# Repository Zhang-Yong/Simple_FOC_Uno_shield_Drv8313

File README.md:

# Simple_FOC_Uno_shield_Drv8313
My Open Source Arduion Uno R3 BLDC FOC shield, use Drv8313 chip
KICAD5 Source file 
Optimze Layout, connect DGND with DRV8313 GND,adding I2C connector for AS5600
Tested work with simplefoc Arduino software
A Try Version for my standalone customerized FOC controller

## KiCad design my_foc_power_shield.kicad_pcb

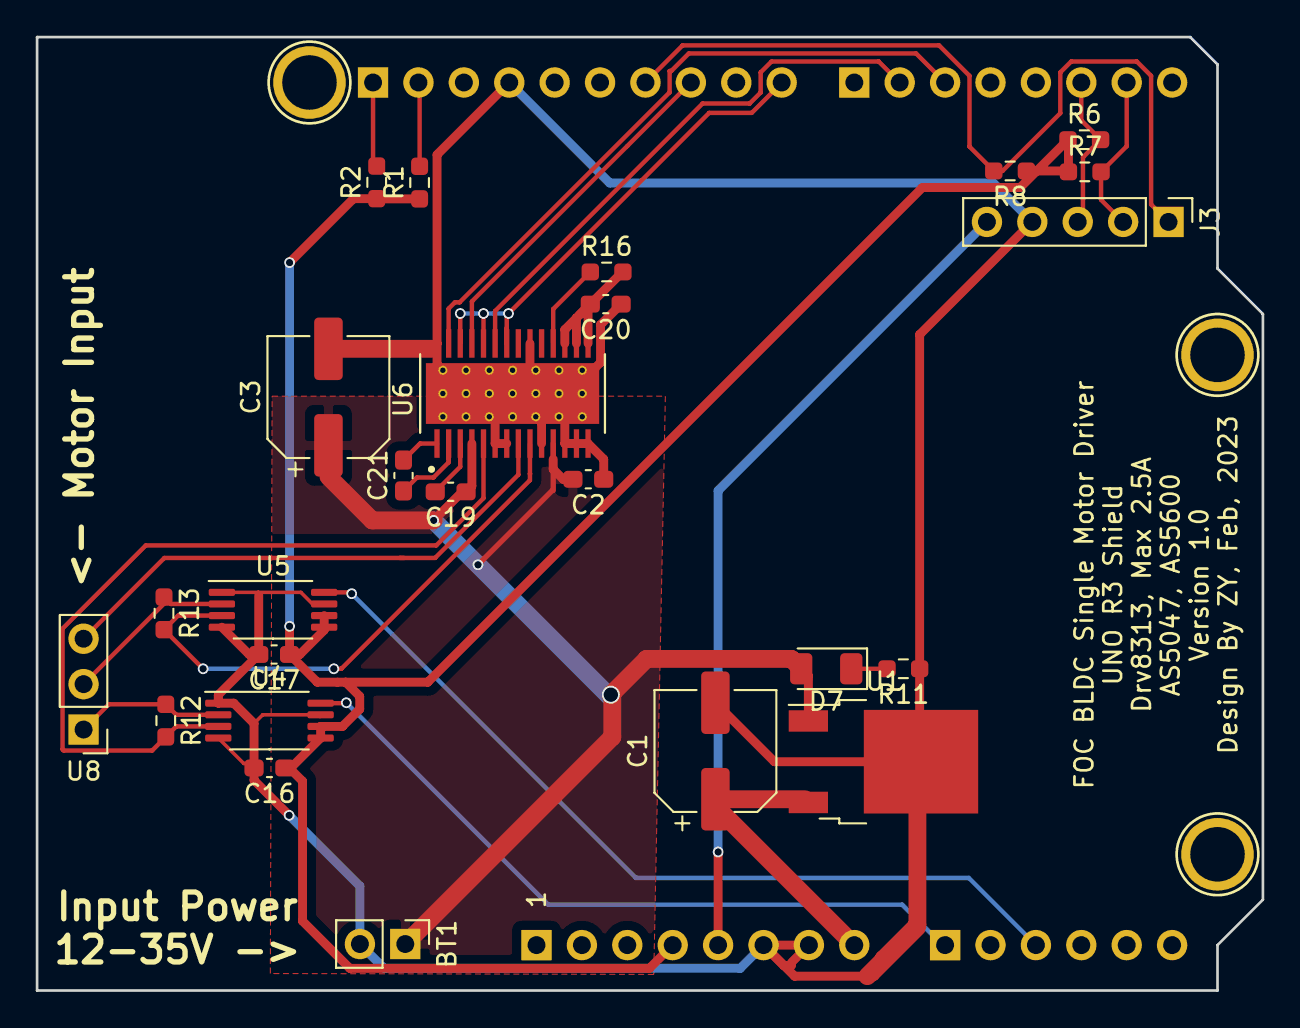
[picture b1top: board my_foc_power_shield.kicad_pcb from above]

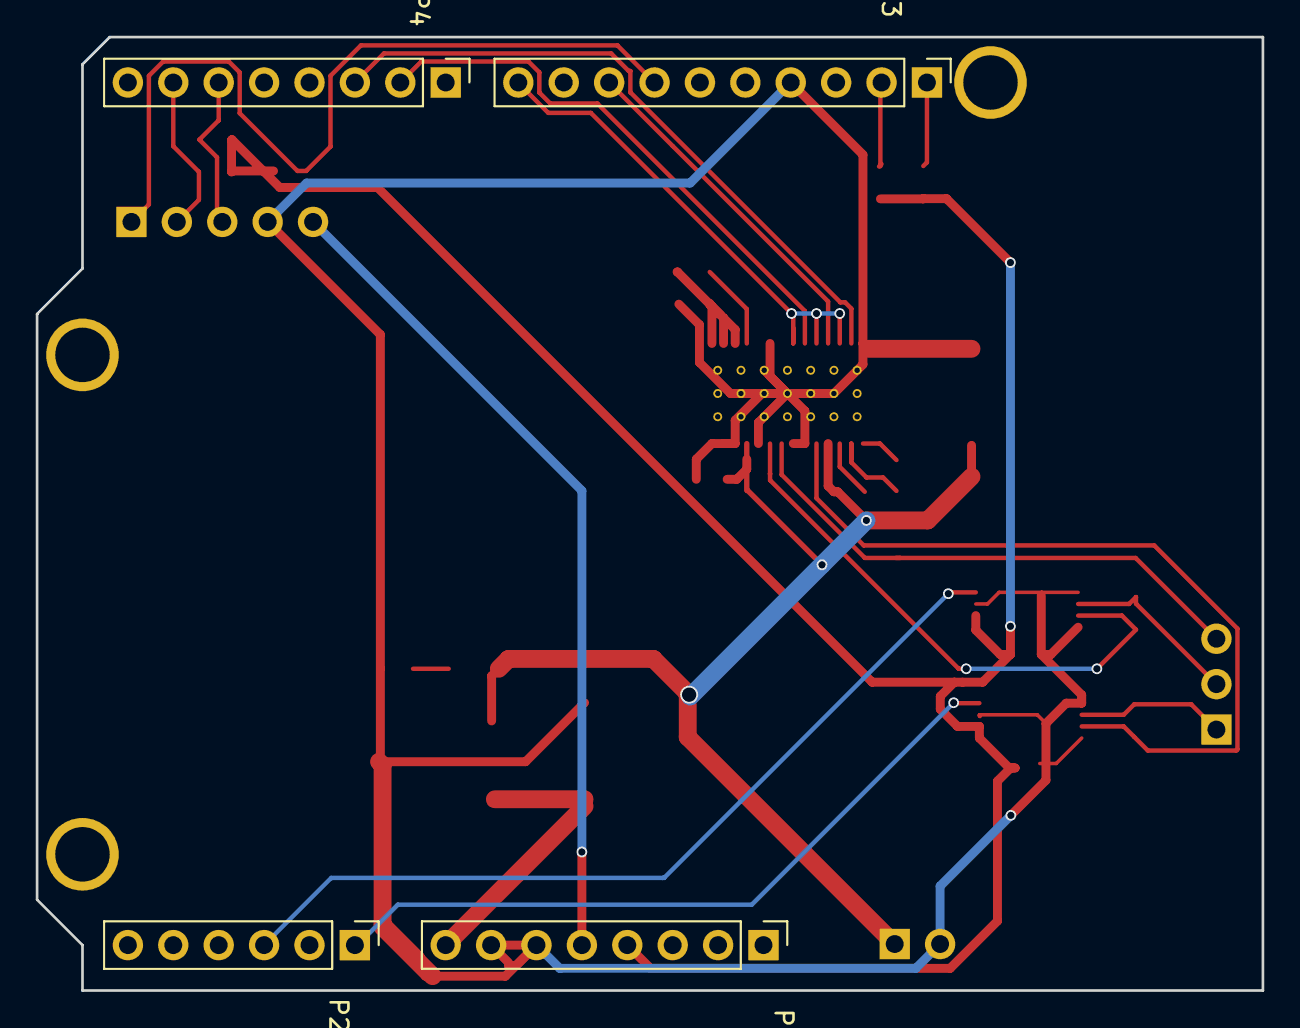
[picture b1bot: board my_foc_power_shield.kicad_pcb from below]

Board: 2 copper layers, 68.6 x 53.3 mm, 32 parts (4 on the bottom side), 27 nets.

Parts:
BT1: Battery; PinHeader_1x02_P2.54mm_Vertical
C1, C3: 100u,50V; CP_Elec_6.3x7.7
C2, C16, C17: 0.1u; C_0603_1608Metric_Pad1.08x0.95mm_HandSolder
C19: 0.1uF; C_0603_1608Metric_Pad1.08x0.95mm_HandSolder
C20: 0.47 uF; C_0603_1608Metric_Pad1.08x0.95mm_HandSolder
C21: 10nF; C_0603_1608Metric_Pad1.08x0.95mm_HandSolder
D7: LED; LED_1206_3216Metric
J3: AS5047; PinHeader_1x05_P2.54mm_Vertical
P1: Power; PinHeader_1x08_P2.54mm_Vertical
P2: Analog; PinHeader_1x06_P2.54mm_Vertical
P3: Digital; PinHeader_1x10_P2.54mm_Vertical
P4: Digital; PinHeader_1x08_P2.54mm_Vertical
P6, P7, P8: CONN_01X01; Arduino_1pin
R1, R2, R6, R7, R8: 3.3K; R_0603_1608Metric_Pad0.98x0.95mm_HandSolder
R11: 2K; R_0603_1608Metric_Pad0.98x0.95mm_HandSolder
R12, R13: 0.01R; R_0603_1608Metric_Pad0.98x0.95mm_HandSolder
R16: 10K; R_0603_1608Metric_Pad0.98x0.95mm_HandSolder
U1: L7808; TO-252-2
U4, U5: INA240A2PW; TSSOP-8_4.4x3mm_P0.65mm
U6: DRV8313PWP; drv8313pwp
U8: Motor Inputs; PinHeader_1x03_P2.54mm_Vertical

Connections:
+3V3: C16.1, C17.1, P1.4, R1.1, R2.1, R6.1, R7.1, R8.1, U4.5, U4.6, U5.5, U5.6
+5V: J3.5, P1.5
/DRV_EN_8: P3.10, U6.22, U6.24, U6.26
/DRV_FAULT: R16.1, U6.18
/Encoder_A_D2: J3.3, P4.6, R6.2
/Encoder_B_D1: J3.2, P4.7, R7.2
/Encoder_Z_D11: J3.1, P3.7, R8.2
/MOTOR_A: R12.1, U4.2, U8.1
/MOTOR_A_CS: R12.2, U4.3, U6.5
/MOTOR_B: R13.1, U5.2, U8.2
/MOTOR_B_CS: R13.2, U5.3, U6.9
/MOTOR_C: U6.8, U8.3
/PWM_A_5: P4.3, U6.27
/PWM_B_10: P3.8, U6.25
/PWM_C_6: P4.2, U6.23
/SCL: P3.1, R2.2
/SDA: P3.2, R1.2
/SENSE_A_A0: P2.1, U4.8
/SENSE_B_A2: P2.3, U5.8
/V3P3: C20.2, R16.2, U6.15, U6.16, U6.17
/Vin: C1.1, P1.8, U1.3
GNDA: BT1.2, C1.2, C2.1, C3.2, C16.2, C17.2, C20.1, J3.4, P1.6, P1.7, P3.4, R11.1, U1.2, U4.1, U4.4, U4.7, U5.1, U5.4, U5.7, U6.6, U6.7, U6.10, U6.12, U6.13, U6.14, U6.20, U6.28, U6.29
unnamed: C19.2, U6.3
unnamed: C21.1, U6.2
unnamed: C21.2, U6.1
unnamed: D7.1, R11.2
VCC_IN: BT1.1, C2.2, C3.1, C19.1, D7.2, U1.1, U6.4, U6.11

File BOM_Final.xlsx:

Designator | Footprint | Comment | 嘉立创元件编号 | FootPrint | Unit Price
C1 | CP_Elec_6.3x7.7 | 电解电容100u,50V | C165974 | 6.3x7.7mm | 2.35
C2 | C_0603_1608Metric_Pad1.08x0.95mm_HandSolder | 0.1u | C1591 | 0603 | 0.01
C3 | CP_Elec_6.3x7.7 | 电解电容100u,50V | C165974 | 6.3x7.7mm | 2.35
C16 | C_0603_1608Metric_Pad1.08x0.95mm_HandSolder | 0.1u | C1591 | 0603 | 0.01
C17 | C_0603_1608Metric_Pad1.08x0.95mm_HandSolder | 0.1u | C1591 | 0603 | 0.01
C19 | C_0603_1608Metric_Pad1.08x0.95mm_HandSolder | 0.1uF | C1591 | 0603 | 0.01
C20 | C_0603_1608Metric_Pad1.08x0.95mm_HandSolder | 0.47_uF | C1623 | 0603 | 0.3
C21 | C_0603_1608Metric_Pad1.08x0.95mm_HandSolder | 10nF | C1589 | 0603 | 0.01
D7 | LED_1206_3216Metric | LED | C84270 | 1206 | 0.13
R1 | R_0603_1608Metric_Pad0.98x0.95mm_HandSolder | 3.3K | C22978 | 0603 | 5.0000000000000001E-3
R2 | R_0603_1608Metric_Pad0.98x0.95mm_HandSolder | 3.3K | C22978 | 0603 | 5.0000000000000001E-3
R6 | R_0603_1608Metric_Pad0.98x0.95mm_HandSolder | 3.3K | C22978 | 0603 | 5.0000000000000001E-3
R7 | R_0603_1608Metric_Pad0.98x0.95mm_HandSolder | 3.3K | C22978 | 0603 | 5.0000000000000001E-3
R8 | R_0603_1608Metric_Pad0.98x0.95mm_HandSolder | 3.3K | C22978 | 0603 | 5.0000000000000001E-3
R11 | R_0603_1608Metric_Pad0.98x0.95mm_HandSolder | 2K | C22975 | 0603 | 6.0000000000000001E-3
R12 | R_0603_1608Metric_Pad0.98x0.95mm_HandSolder | 0.01R, SEI,电流采样电阻 | C346485 | 0603 | 1.6
R13 | R_0603_1608Metric_Pad0.98x0.95mm_HandSolder | 0.01R, SEI,电流采样电阻 | C346485 | 0603 | 1.6
R16 | R_0603_1608Metric_Pad0.98x0.95mm_HandSolder | 10K | C25804 | 0603 | 5.0000000000000001E-3
U1 | TO-252-2 | L78M08,DPAK,ST | C158076 | DPAK,T0-252-2 | 1.5
U4 | TSSOP-8_4.4x3mm_P0.65mm | INA240A2PW | C527535 | SOIC-8,4.4X3mm | 10
U5 | TSSOP-8_4.4x3mm_P0.65mm | INA240A2PW | C527535 | SOIC-8,4.4X3mm | 10
U6 | DRV8313PWPR | TI 电机驱动芯片 | C92482 | HTSSOP-28-EP-4.5mm | 12

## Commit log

2023-02-19 Add files via upload
    Kicad design file, includes schematic and pcb
2023-02-19 Add files via upload
    Gerbe file
2023-03-06 Update README.md
    Optimize layout, adding AS5600 connector
    Test work with simplefoc Arduino Software
2023-03-06 Add files via upload
    Update V2 Version of KICAD schematic and layout file
2023-03-06 Add files via upload
    V2 BOM File
2023-09-18 Update README.md
    Update Readme
